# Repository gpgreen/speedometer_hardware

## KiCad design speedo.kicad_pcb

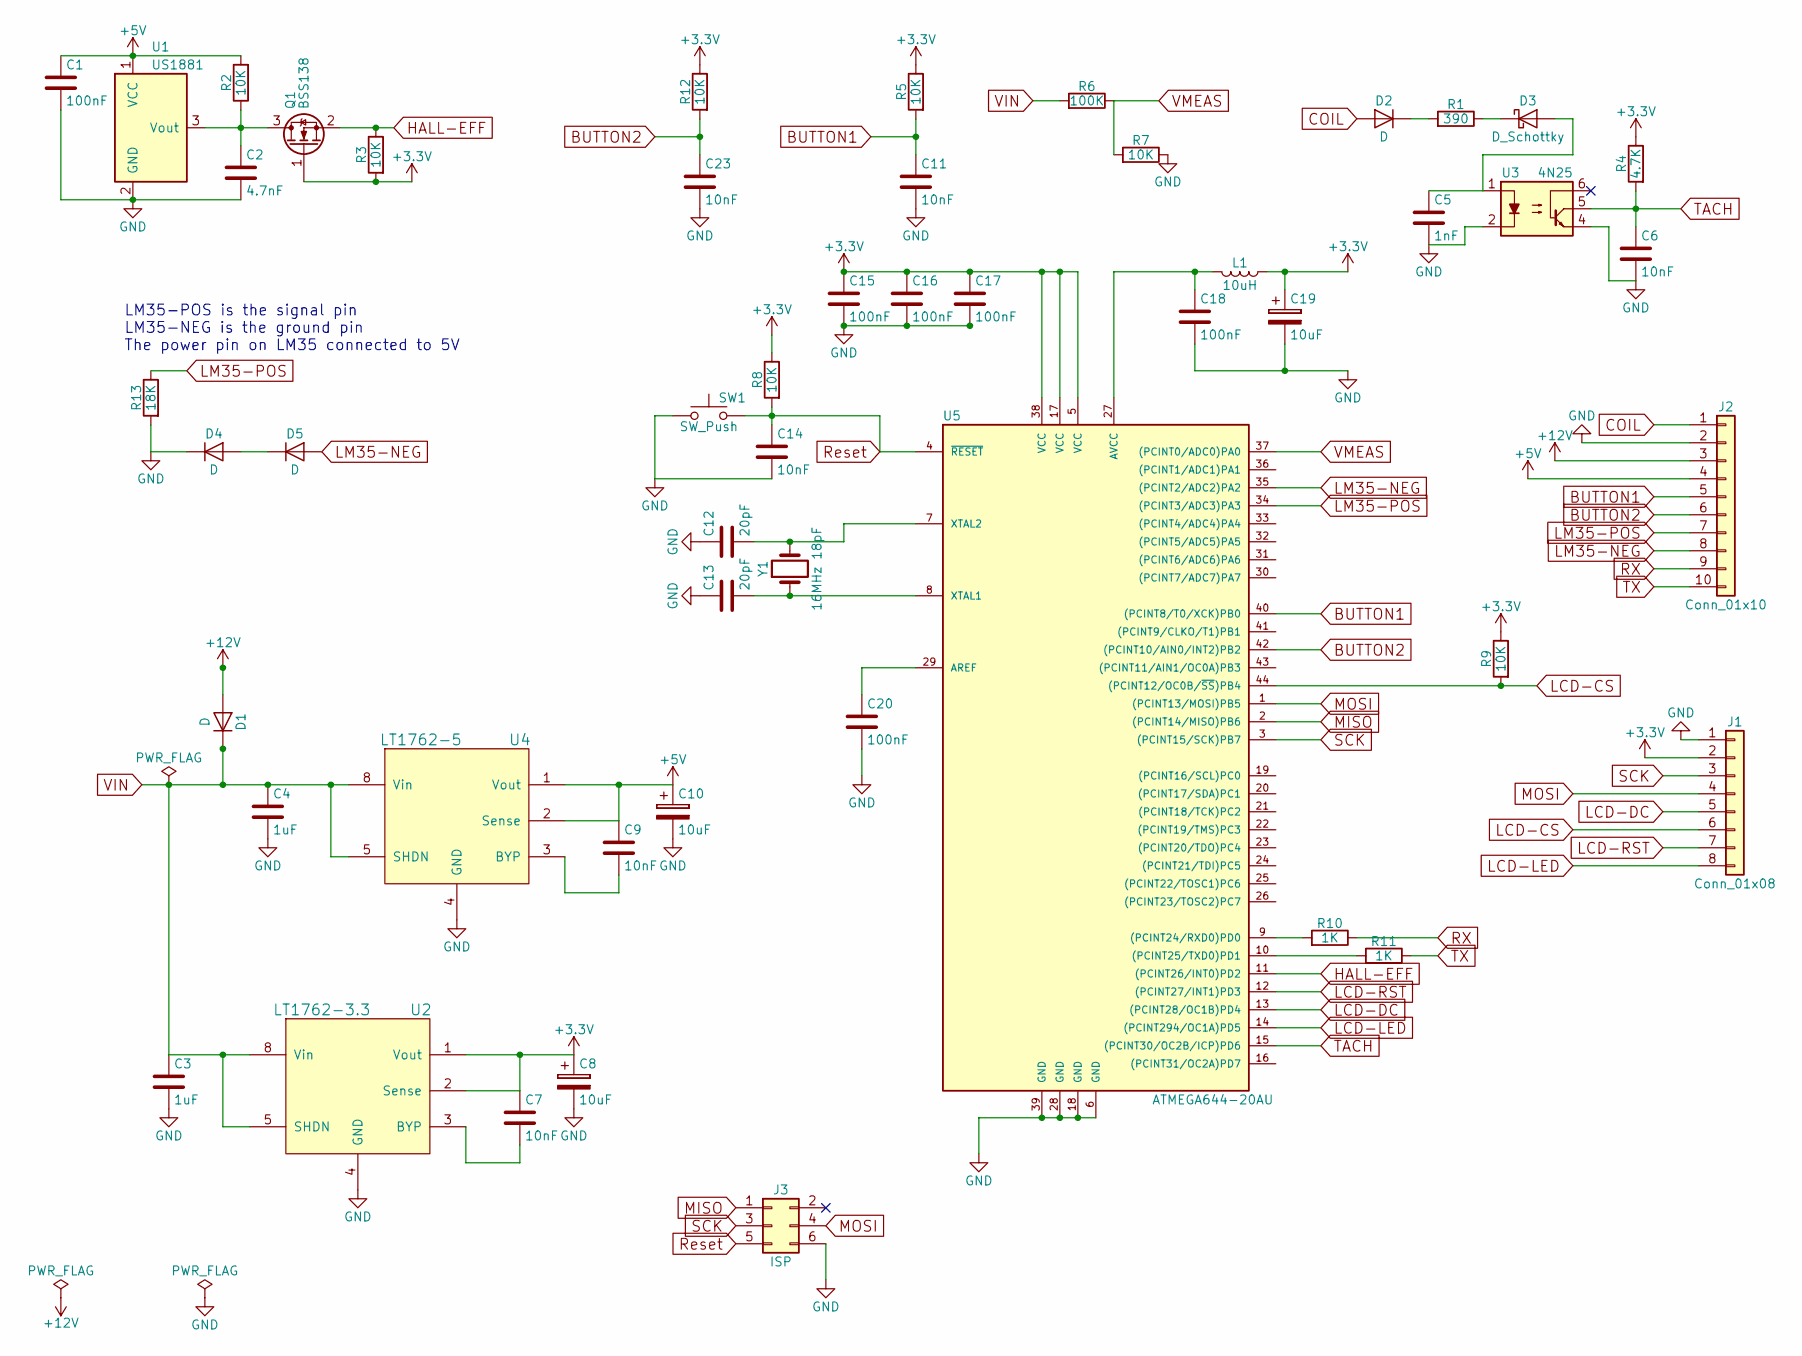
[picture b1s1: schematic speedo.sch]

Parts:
C1, C15, C16, C17, C18, C20: 100nF; C_0603
C2: 4.7nF; C_0603
C3, C4: 1uF; C_1206
C5: 1nF; C_1206
C6, C11, C14, C23: 10nF; C_0603
C7, C9: 10nF; C_1206
C8, C10, C19: 10uF; CP_Tantalum_Case-A_EIA-3216-18_Reflow
C12, C13: 20pF; C_0603
D1, D2, D4, D5: D; D_SOD-123F
D3: D_Schottky; D_SOD-123F
J1: Conn_01x08; Molex_PicoBlade_53398-0871_08x1.25mm_Straight
J2: Conn_01x10; Molex_PicoBlade_53398-1071_10x1.25mm_Straight
J3: ISP
L1: 10uH; L_1206
Q1: BSS138; SOT-23
R1: 390; R_1206
R2, R3, R5, R7, R8, R9, R12: 10K; R_0603
R4: 4.7K; R_0603
R6: 100K; R_0603
R10, R11: 1K; R_0603
R13: 18K; R_0603
SW1: SW_Push; switch-kpt-1187B-SMD
U1: US1881; TO-92-pins-3-in-a-row
U2: LT1762-3.3; MSOP-8_3x3mm_Pitch0.65mm
U3: 4N25; 4N2X
U4: LT1762-5; MSOP-8_3x3mm_Pitch0.65mm
U5: ATMEGA644-20AU; TQFP-44_10x10mm_Pitch0.8mm
Y1: 16MHz 18pF; Crystal_SMD_HC49-SD

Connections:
+3V3: C7.1, C8.1, C15.1, C16.1, C17.1, C19.1, J1.2, L1.1, Q1.1 (G), R3.2, R4.1, R5.1, R8.1, R9.1, R12.1, U2.1 (Vout), U2.2 (Sense), U5.5 (VCC), U5.17 (VCC), U5.38 (VCC)
+5V: C1.1, C9.1, C10.1, J2.4, R2.2, U1.1 (VCC), U4.1 (Vout), U4.2 (Sense)
+12V: D1.2 (A), J2.3
BUTTON1: C11.1, J2.5, R5.2, U5.40 ((PCINT8/T0/XCK)PB0)
BUTTON2: C23.1, J2.6, R12.2, U5.42 ((PCINT10/AIN0/INT2)PB2)
COIL: D2.2 (A), J2.1
GND: C1.2, C2.2, C3.2, C4.2, C5.2, C6.2, C8.2, C10.2, C11.2, C12.1, C13.1, C14.2, C15.2, C16.2, C17.2, C18.2, C19.2, C20.2, C23.2, D4.1 (K), J1.1, J2.2, J3.6, R7.1, R13.2, SW1.1, U1.2 (GND), U2.4 (GND), U3.2, U3.4, U4.4 (GND), U5.6 (GND), U5.18 (GND), U5.28 (GND), U5.39 (GND)
HALL-EFF: Q1.2 (S), R3.1, U5.11 ((PCINT26/INT0)PD2)
LCD-CS: J1.6, R9.2, U5.44 ((PCINT12/OC0B/~SS~)PB4)
LCD-DC: J1.5, U5.13 ((PCINT28/OC1B)PD4)
LCD-LED: J1.8, U5.14 ((PCINT294/OC1A)PD5)
LCD-RST: J1.7, U5.12 ((PCINT27/INT1)PD3)
LM35-NEG: D5.2 (A), J2.8, U5.35 ((PCINT2/ADC2)PA2)
LM35-POS: J2.7, R13.1, U5.34 ((PCINT3/ADC3)PA3)
MISO: J3.1, U5.2 ((PCINT14/MISO)PB6)
MOSI: J1.4, J3.4, U5.1 ((PCINT13/MOSI)PB5)
unnamed: C2.1, Q1.3 (D), R2.1, U1.3 (Vout)
unnamed: C5.1, D3.2 (A), U3.1
unnamed: C7.2, U2.3 (BYP)
unnamed: C9.2, U4.3 (BYP)
unnamed: C12.2, U5.7 (XTAL2), Y1.2
unnamed: C13.2, U5.8 (XTAL1), Y1.1
unnamed: C18.1, L1.2, U5.27 (AVCC)
unnamed: C20.1, U5.29 (AREF)
unnamed: D2.1 (K), R1.2
unnamed: D3.1 (K), R1.1
unnamed: D4.2 (A), D5.1 (K)
unnamed: R10.2, U5.9 ((PCINT24/RXD0)PD0)
unnamed: R11.2, U5.10 ((PCINT25/TXD0)PD1)
RX: J2.9, R10.1
Reset: C14.1, J3.5, R8.2, SW1.2, U5.4 (~RESET)
SCK: J1.3, J3.3, U5.3 ((PCINT15/SCK)PB7)
TACH: C6.1, R4.2, U3.5, U5.15 ((PCINT30/OC2B/ICP)PD6)
TX: J2.10, R11.1
VIN: C3.1, C4.1, D1.1 (K), R6.2, U2.5 (SHDN), U2.8 (Vin), U4.5 (SHDN), U4.8 (Vin)
VMEAS: R6.1, R7.2, U5.37 ((PCINT0/ADC0)PA0)

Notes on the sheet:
LM35-POS is the signal pin LM35-NEG is the ground pin The power pin on LM35 connected to 5V

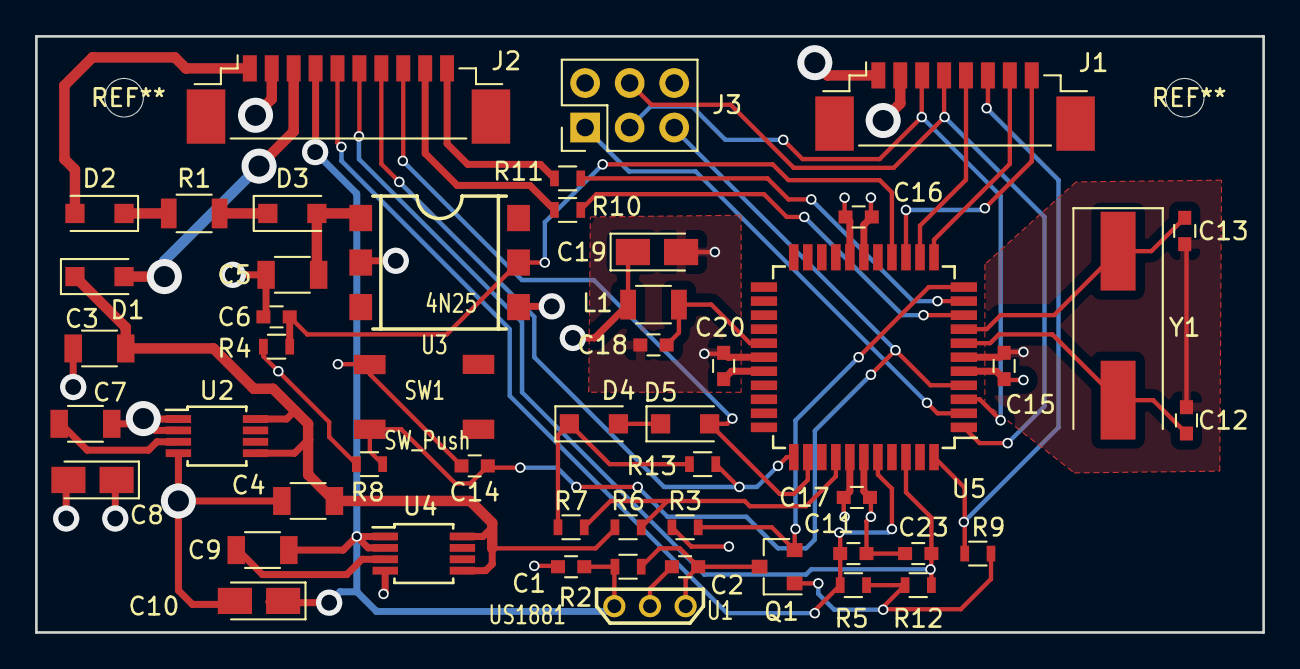
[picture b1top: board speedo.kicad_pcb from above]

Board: 4 copper layers, 70.0 x 34.0 mm, 51 parts (0 on the bottom side), 36 nets.

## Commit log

2018-07-04 Changed to atmel design
2018-07-06 Removed traces, redid placement
2018-07-10 changed atmega644 to atmega328
2018-07-12 Fixed footprints
2018-07-13 Moved ref des for clarity
2018-07-22 Moved some pins around
2018-07-23 Finished first layout of pcb
2018-07-31 Added caption
2018-08-18 Fixed solder mask clearance
2018-08-18 Merged atmega644
2018-10-05 Updated version of pcb due to clearance change
2018-10-05 Fixed ISP programmer and traces
2018-10-06 Moved refdes labels around
